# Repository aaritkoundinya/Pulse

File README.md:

# Pulse

Single-repo KiCad workspace for all Pulse board revisions.

## Repository Structure

- `boards/r2/` - imported from your existing `pulser2`
- `boards/r2.1/` - imported from your existing `pulser2.1`
- `templates/scratch-board/` - starter template for clean-slate revisions
- `tools/new_revision.sh` - helper script to create new revisions

Each board folder has its own KiCad-focused `.gitignore`.

## Create New Revisions

Build from an existing revision:

```bash
./tools/new_revision.sh r3 --from r2.1
```

Start from scratch:

```bash
./tools/new_revision.sh r3 --scratch
```

After creation, open KiCad and work in `boards/<revision>/`.

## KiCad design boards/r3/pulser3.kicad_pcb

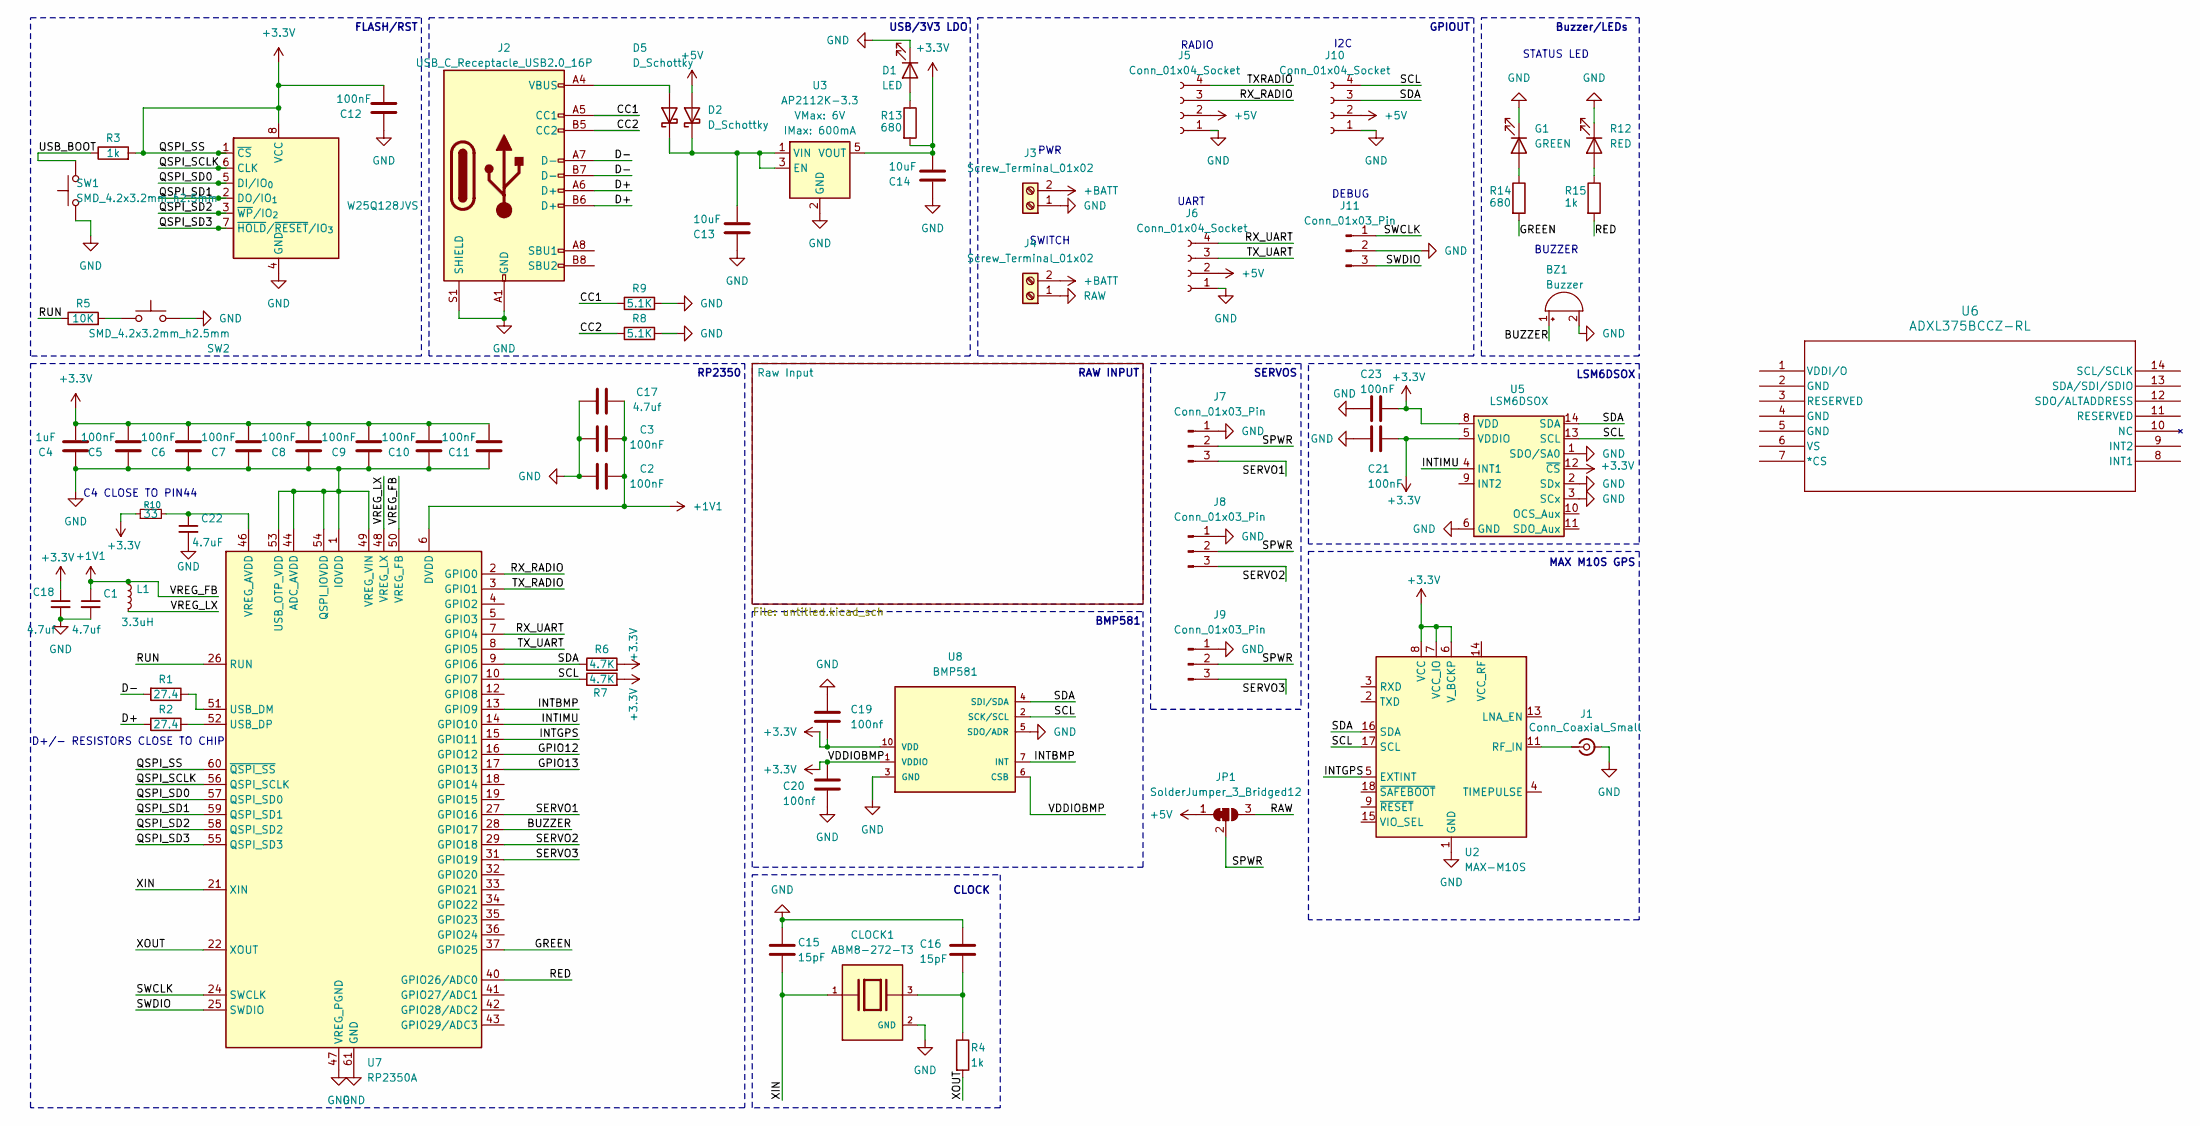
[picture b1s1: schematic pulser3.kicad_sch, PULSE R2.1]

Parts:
BZ1: Buzzer; Buzzer_CUI_CPT-9019S-SMT
C1, C17, C18: 4.7uf; C_0402_1005Metric
C2, C3, C5, C6, C7, C8, C9, C10, C11, C12, C21, C23: 100nF; C_0402_1005Metric
C4: 1uF; C_0402_1005Metric
C13, C14: 10uF; C_0805_2012Metric
C15, C16: 15pF; C_0402_1005Metric
C19, C20: 100nf; C_0402_1005Metric
C22: 4.7uF; C_0402_1005Metric
CLOCK1: ABM8-272-T3; XTAL_ABM8-272-T3; PARTREV 07-29-20
D1: LED; LED_0603_1608Metric
D2, D5: D_Schottky; D_SOD-323_HandSoldering
G1: GREEN; LED_0603_1608Metric
J1: Conn_Coaxial_Small; U.FL_Molex_MCRF_73412-0110_Vertical
J2: USB_C_Receptacle_USB2.0_16P; USB_C_Receptacle_JAE_DX07S016JA1R1500
J3, J4: Screw_Terminal_01x02; TerminalBlock_Phoenix_MPT-0,5-2-2.54_1x02_P2.54mm_Horizontal
J5, J6, J10: Conn_01x04_Socket; JST_SH_BM04B-SRSS-TB_1x04-1MP_P1.00mm_Vertical
J7, J8, J9, J11: Conn_01x03_Pin; JST_SH_BM03B-SRSS-TB_1x03-1MP_P1.00mm_Vertical
JP1: SolderJumper_3_Bridged12; SolderJumper-3_P1.3mm_Open_RoundedPad1.0x1.5mm
L1: 3.3uH; Untitled
R1, R2: 27.4; R_0402_1005Metric
R3, R4, R15: 1k; R_0402_1005Metric
R5: 10K; R_0402_1005Metric
R6, R7: 4.7K; R_0402_1005Metric
R8, R9: 5.1K; R_0402_1005Metric
R10: 33; R_0402_1005Metric
R12: RED; LED_0603_1608Metric
R13, R14: 680; R_0402_1005Metric
SW1, SW2: SMD_4.2x3.2mm_h2.5mm; Push_SMD_4.2x3.2mm
U1: W25Q128JVS; WSON-8-1EP_6x5mm_P1.27mm_EP3.4x4.3mm
U2: MAX-M10S; ublox_MAX
U3: AP2112K-3.3; SOT23-5
U5: LSM6DSOX; ST_LGA-14L_2.5x3.0mm_P0.5mm_4x3
U6: ADXL375BCCZ-RL
U7: RP2350A; QFN-60-1EP_7x7mm_P0.4mm_EP3.4x3.4mm
U8: BMP581

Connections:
+1V1: C1.1, C2.2, C3.2, C17.2, L1.1, U7.6 (DVDD), U7.23 (DVDD), U7.39 (DVDD), U7.50 (VREG_FB)
+3.3V: C4.1, C5.1, C6.1, C7.1, C8.1, C9.1, C10.1, C11.1, C12.1, C14.1, C18.1, C19.2, C20.1, C21.2, C23.2, R3.2, R6.2, R7.2, R10.1, R13.2, U1.1 (~CS), U1.8 (VCC), U2.6 (V_BCKP), U2.7 (VCC_IO), U2.8 (VCC), U3.5 (VOUT), U5.5 (VDDIO), U5.8 (VDD), U5.12 (~CS), U7.60 (~QSPI_SS), U8.1 (VDDIO), U8.6 (CSB), U8.10 (VDD)
+5V: D2.2 (A), J5.2, J6.2, J10.2, JP1.1 (A)
+BATT: J3.2, J4.2
/BUZZER: BZ1.1 (+), U7.28 (GPIO17)
/CC1: J2.A5 (CC1), R9.1
/CC2: J2.B5 (CC2), R8.1
/D+: J2.A6 (D+), J2.B6 (D+), R2.2
/D-: J2.A7 (D-), J2.B7 (D-), R1.2
/GPIO12: U7.16 (GPIO12)
/GPIO13: U7.17 (GPIO13)
/GREEN: R14.2, U7.37 (GPIO25)
/INTBMP: U7.13 (GPIO9), U8.7 (INT)
/INTGPS: U2.5 (EXTINT), U7.15 (GPIO11)
/INTIMU: U5.4 (INT1), U7.14 (GPIO10)
/QSPI_SCLK: U1.6 (CLK), U7.56 (QSPI_SCLK)
/QSPI_SD0: U1.5 (DI/IO_{0}), U7.57 (QSPI_SD0)
/QSPI_SD1: U1.2 (DO/IO_{1}), U7.59 (QSPI_SD1)
/QSPI_SD2: U1.3 (~WP/IO_{2}), U7.58 (QSPI_SD2)
/QSPI_SD3: U1.7 (~HOLD/~RESET/IO_{3}), U7.55 (QSPI_SD3)
/RED: R15.2, U7.40 (GPIO26/ADC0)
/RUN: R5.1, U7.26 (RUN)
/RX_RADIO: J5.3, U7.2 (GPIO0)
/RX_UART: J6.4, U7.7 (GPIO4)
/SCL: J10.4, R7.1, U2.17 (SCL), U5.13 (SCL), U7.10 (GPIO7), U8.2 (SCK/SCL)
/SDA: J10.3, R6.1, U2.16 (SDA), U5.14 (SDA), U7.9 (GPIO6), U8.4 (SDI/SDA)
/SERVO1: J7.3, U7.27 (GPIO16)
/SERVO2: J8.3, U7.29 (GPIO18)
/SERVO3: J9.3, U7.31 (GPIO19)
/SPWR: J7.2, J8.2, J9.2, JP1.2 (C)
/SWCLK: J11.1, U7.24 (SWCLK)
/SWDIO: J11.3, U7.25 (SWDIO)
/TXRADIO: J5.4
/TX_RADIO: U7.3 (GPIO1)
/TX_UART: J6.3, U7.8 (GPIO5)
/USB_BOOT: R3.1, SW1.2
/VREG_LX: L1.2, U7.48 (VREG_LX)
/XIN: C15.2, CLOCK1.1, U7.21 (XIN)
/XOUT: R4.2, U7.22 (XOUT)
GND: BZ1.2 (-), C1.2, C2.1, C3.1, C4.2, C5.2, C6.2, C7.2, C8.2, C9.2, C10.2, C11.2, C12.2, C13.2, C14.2, C15.1, C16.1, C17.1, C18.2, C19.1, C20.2, C21.1, C22.2, C23.1, CLOCK1.2 (GND), CLOCK1.4 (GND), D1.1 (K), G1.1 (K), J1.2 (Ext), J2.A1 (GND), J2.A12 (GND), J2.B1 (GND), J2.B12 (GND), J2.S1 (SHIELD), J3.1, J5.1, J6.1, J7.1, J8.1, J9.1, J10.1, J11.2, R8.2, R9.2, R12.1 (K), SW1.1, SW2.2, U1.4 (GND), U2.1 (GND), U2.10 (GND), U2.12 (GND), U3.2 (GND), U5.1 (SDO/SA0), U5.2 (SDx), U5.3 (SCx), U5.6 (GND), U5.7 (GND), U7.1 (IOVDD), U7.11 (IOVDD), U7.20 (IOVDD), U7.30 (IOVDD), U7.38 (IOVDD), U7.44 (ADC_AVDD), U7.45 (IOVDD), U7.47 (VREG_PGND), U7.49 (VREG_VIN), U7.53 (USB_OTP_VDD), U7.54 (QSPI_IOVDD), U7.61 (GND), U8.3 (GND), U8.5 (SDO/ADR), U8.8 (GND), U8.9 (GND)
unnamed: C16.2, CLOCK1.3, R4.1
unnamed: D1.2 (A), R13.1
unnamed: C13.1, D2.1 (K), D5.1 (K), U3.1 (VIN), U3.3 (EN)
unnamed: D5.2 (A), J2.A4 (VBUS), J2.A9 (VBUS), J2.B4 (VBUS), J2.B9 (VBUS)
unnamed: G1.2 (A), R14.1
unnamed: J1.1 (In), U2.11 (RF_IN)
unnamed: R5.2, SW2.1
unnamed: R12.2 (A), R15.1
unnamed: R1.1, U7.51 (USB_DM)
unnamed: R2.1, U7.52 (USB_DP)
unnamed: C22.1, R10.2, U7.46 (VREG_AVDD)
RAW: J4.1, JP1.3 (B)

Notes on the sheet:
MAX M10S GPS
PWR
FLASH/RST
RP2350
USB/3V3 LDO
RAW INPUT
D+/- RESISTORS CLOSE TO CHIP
RADIO
C4 CLOSE TO PIN44
BUZZER
SERVOS
I2C
STATUS LED
SWITCH
BMP581
DEBUG
CLOCK
UART
LSM6DSOX
Buzzer/LEDs
GPIOUT

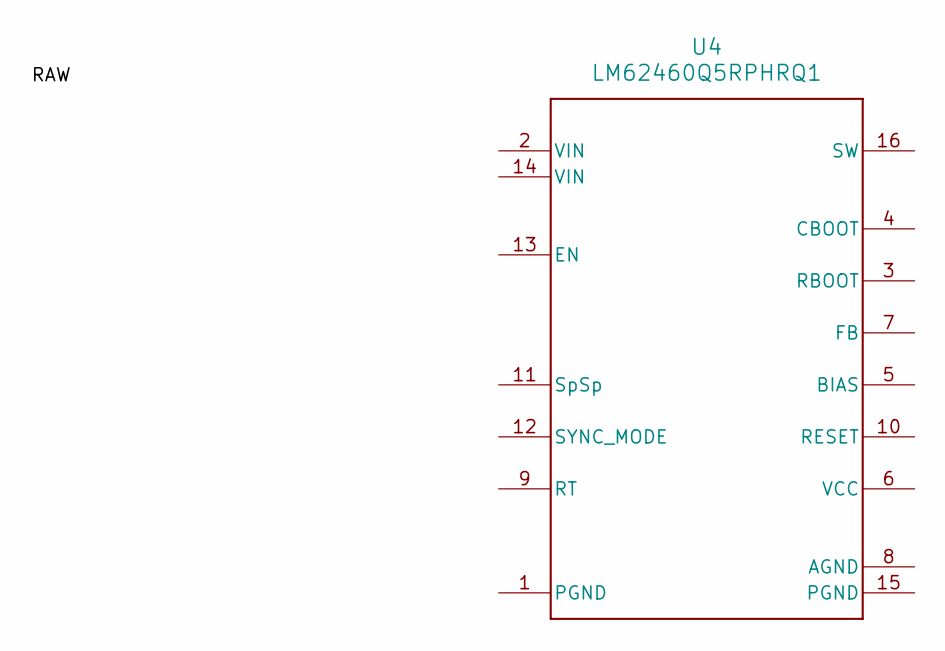
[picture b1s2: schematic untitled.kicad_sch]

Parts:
U4: LM62460Q5RPHRQ1

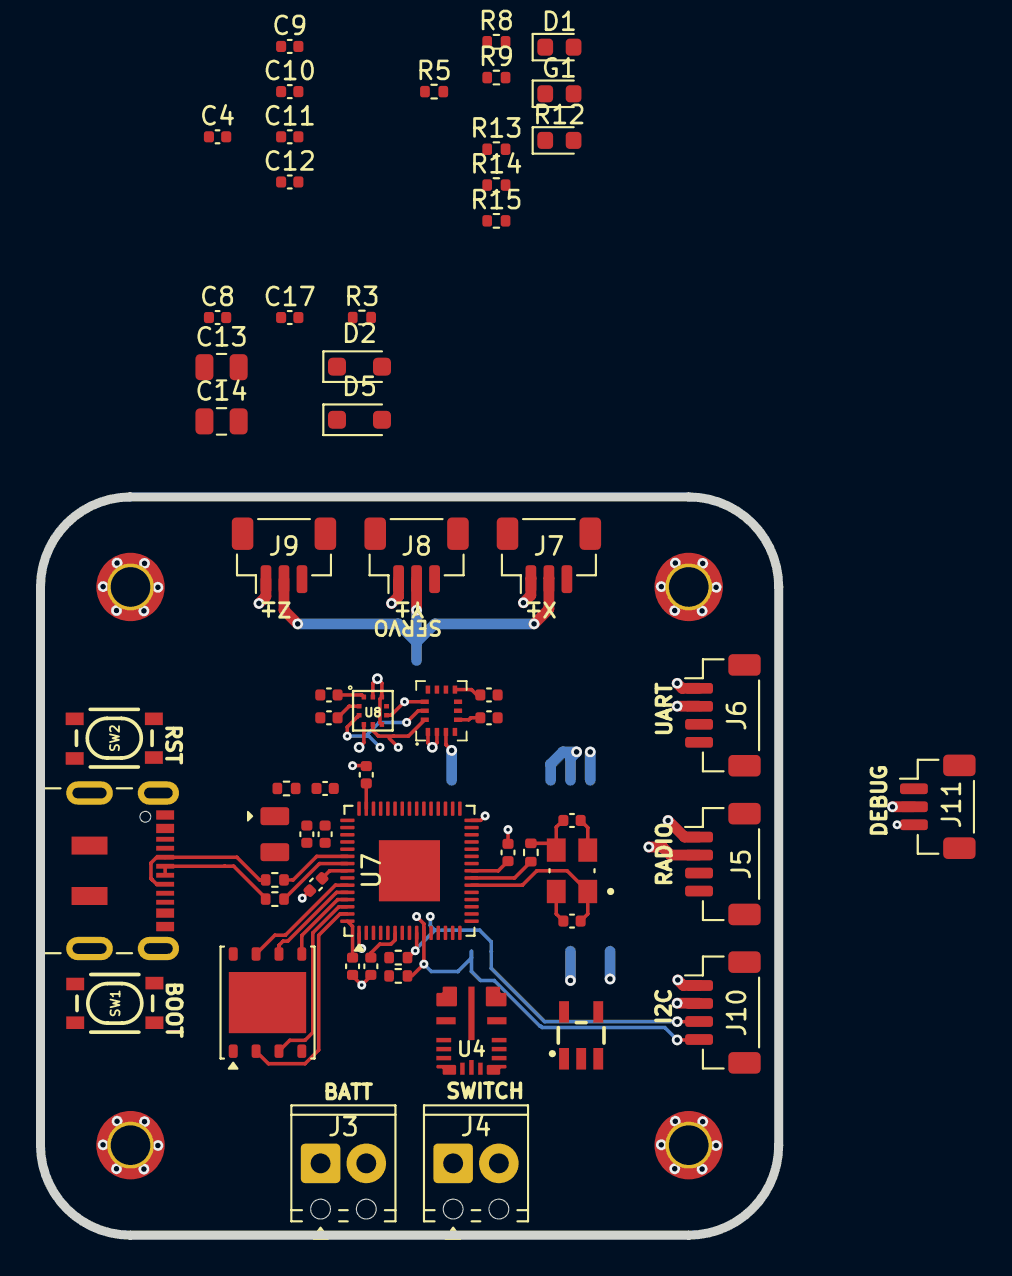
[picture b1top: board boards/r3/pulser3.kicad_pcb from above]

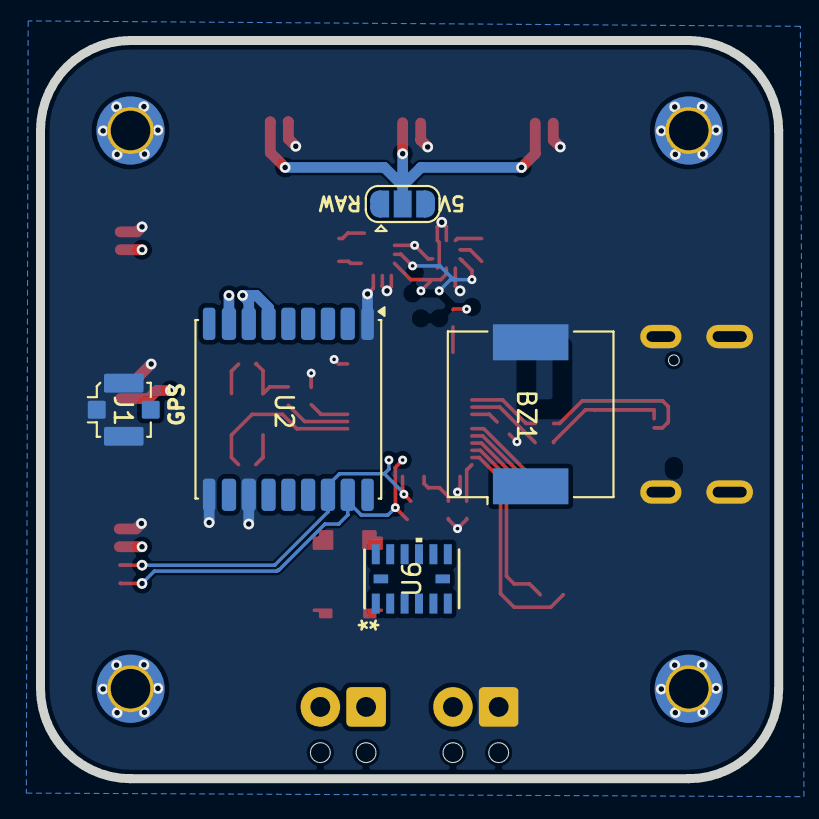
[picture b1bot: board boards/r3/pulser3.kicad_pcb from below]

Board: 4 copper layers, 41.0 x 41.0 mm, 66 parts (5 on the bottom side), 48 nets.

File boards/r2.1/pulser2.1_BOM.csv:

"Id";"Designator";"Footprint";"Quantity";"Designation";"Supplier and ref";
1;"U2";"SOT-23-5";1;"SPX3819M5-L-1-8";;;
2;"C28";"C_0603_1608Metric";1;"10nF";;;
3;"C25";"C_Elec_3x5.4";1;"2.2uF";;;
4;"R3,R4";"R_0603_1608Metric";2;"1k";;;
5;"C16,C15";"C_0603_1608Metric";2;"15pF";;;
6;"R6,R8,R9,R7";"R_0603_1608Metric";4;"4.7K";;;
7;"U1";"QFN-56-1EP_7x7mm_P0.4mm_EP3.2x3.2mm";1;"RP2040";;;
8;"C22,C21,C23";"C_0603_1608Metric";3;"0.1uF";;;
9;"PWR1,SW1";"PinHeader_1x02_P2.54mm_Vertical";2;"Conn_01x02_Pin";;;
10;"C20,C19";"C_0603_1608Metric";2;"100nf";;;
11;"C26,C27";"C_0603_1608Metric";2;"22uF";;;
12;"C17,C13,C14";"C_0603_1608Metric";3;"10uF";;;
13;"BZ1";"MagneticBuzzer_CUI_CMT-8504-100-SMT";1;"Buzzer";;;
14;"U3";"SOT23-5";1;"AP2112K-3.3";;;
15;"C24,C1,C4";"C_0603_1608Metric";3;"1uF";;;
16;"R5,R11";"R_0603_1608Metric";2;"10K";;;
17;"USB1";"USB_Micro-B_Wuerth_629105150521";1;"USB_B_Micro";;;
18;"IMU1";"InvenSense_QFN-24_3x3mm_P0.4mm";1;"ICM-20948";;;
19;"CLOCK1";"XTAL_ABM8-272-T3";1;"ABM8-272-T3";;;
20;"C18,C12,C9,C7,C10,C6,C8,C3,C11,C2,C5";"C_0603_1608Metric";11;"100nF";;;
21;"D2,D5";"D_0603_1608Metric";2;"D_Schottky";;;
22;"L1";"L_0603_1608Metric";1;"2.2uH";;;
23;"G1";"LED_0603_1608Metric";1;"GREEN";;;
24;"BMP1";"BMP581";1;"BMP581";;;
25;"R12";"LED_0603_1608Metric";1;"RED";;;
26;"SERVO1";"PinHeader_1x03_P2.54mm_Horizontal";1;"Conn_01x03_Pin";;;
27;"U6";"SOT-563";1;"AP62250Z6";;;
28;"BOOTSL1,RST1";"Push_SMD_4.2x3.2mm";2;"SMD_4.2x3.2mm_h2.5mm";;;
29;"R1,R2";"R_0603_1608Metric";2;"27.4";;;
30;"FLASH1";"SOIC-8_5.3x5.3mm_P1.27mm";1;"W25Q128JVS";;;
31;"RADIO1,GPIO1";"JST_PH_B4B-PH-K_1x04_P2.00mm_Vertical";2;"Conn_01x04_Socket";;;
32;"R10";"R_0603_1608Metric";1;"52.3K";;;
33;"D1";"LED_0603_1608Metric";1;"LED";;;

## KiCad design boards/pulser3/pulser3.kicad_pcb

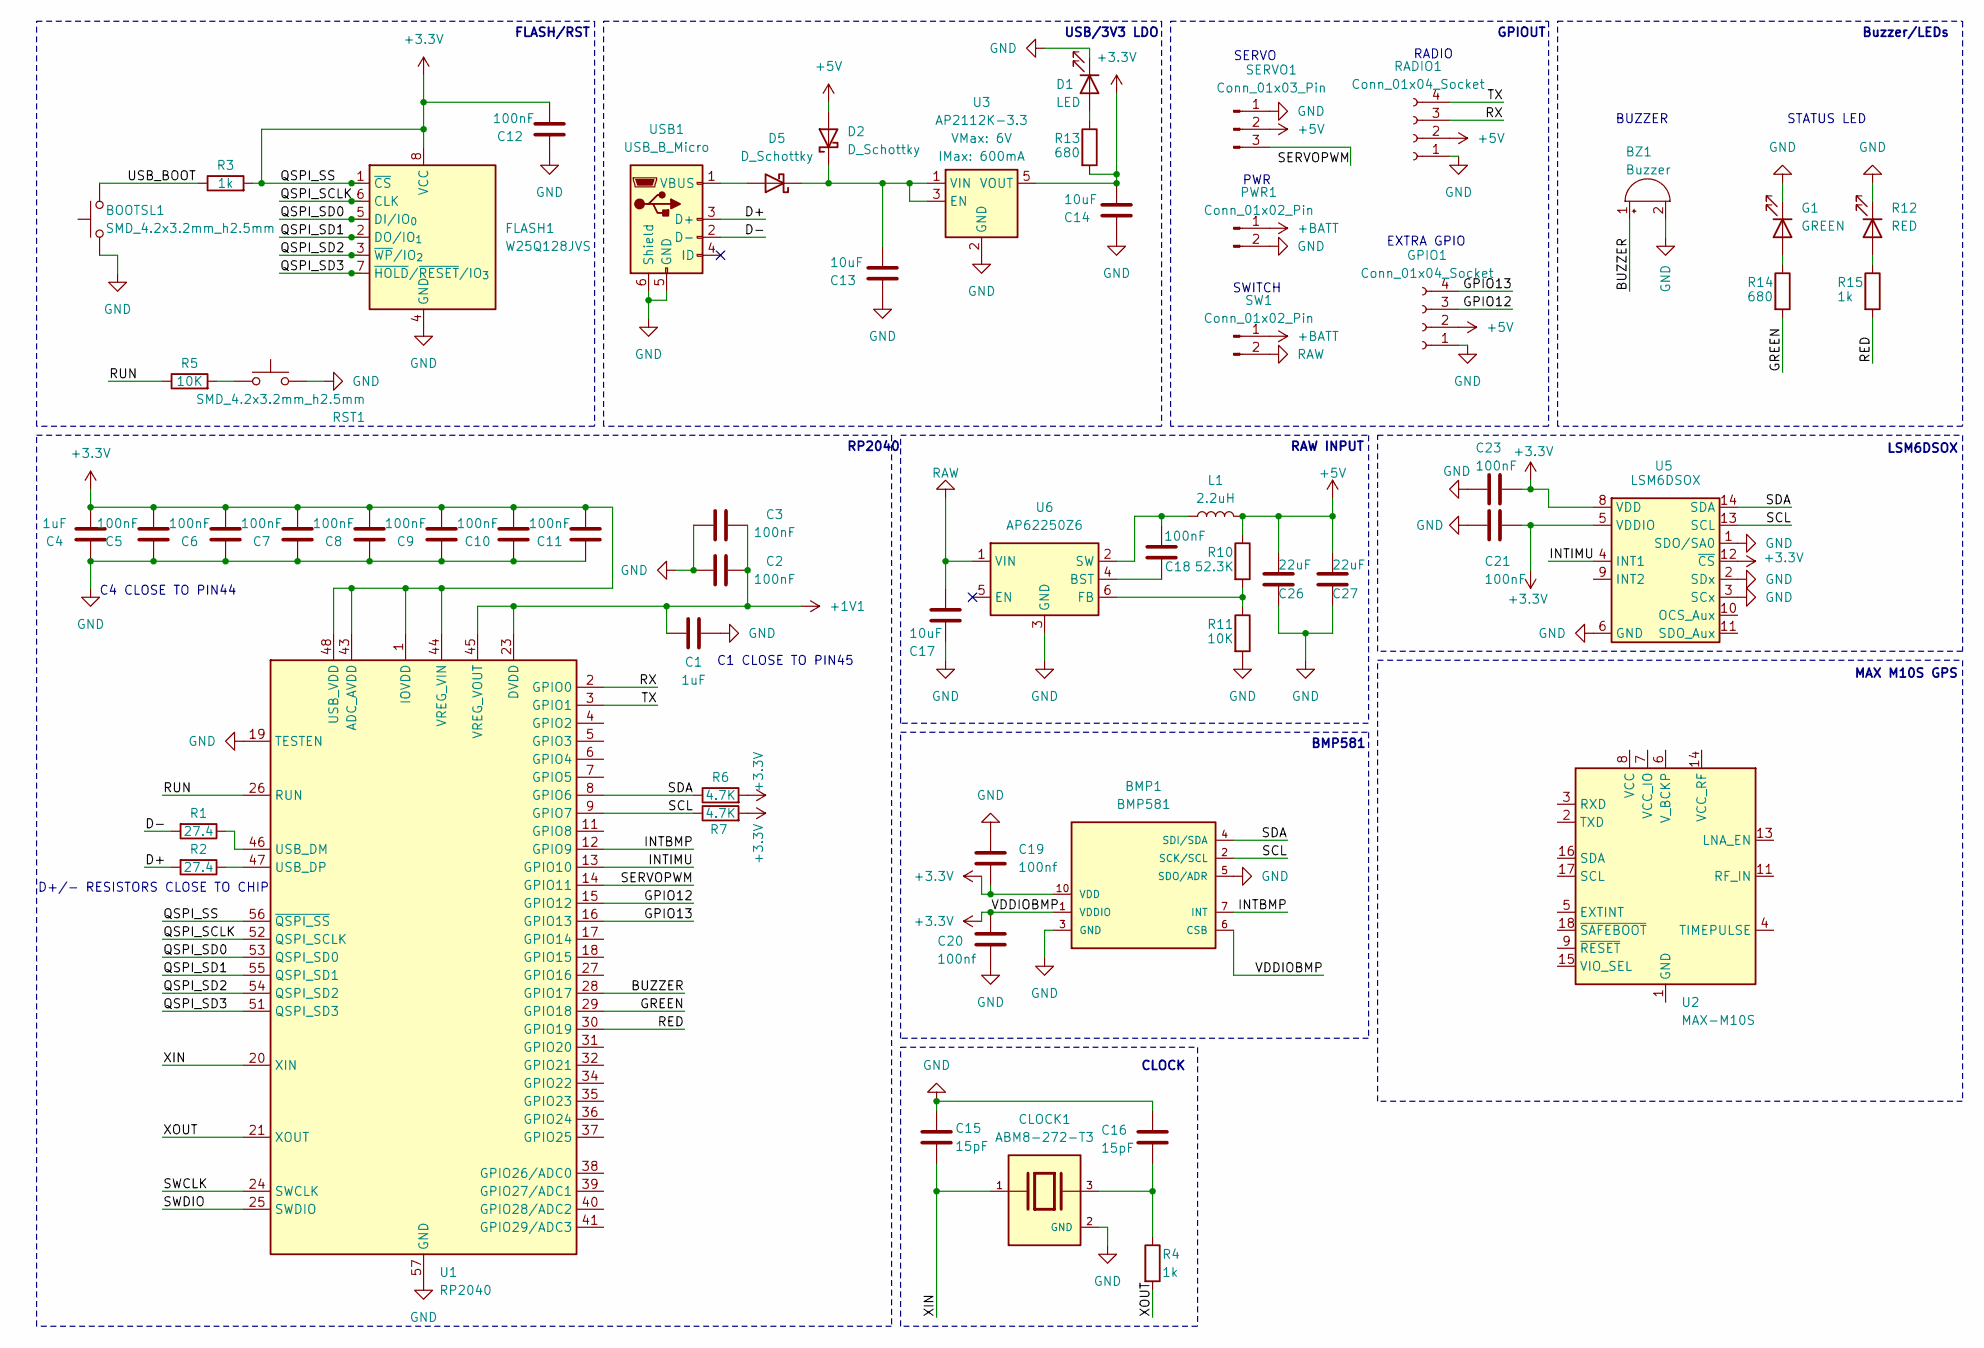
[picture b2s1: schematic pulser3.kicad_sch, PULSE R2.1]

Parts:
BMP1: BMP581
BOOTSL1: SMD_4.2x3.2mm_h2.5mm; Push_SMD_4.2x3.2mm
BZ1: Buzzer; Buzzer_CUI_CPT-9019S-SMT
C1, C4: 1uF; C_0603_1608Metric
C2, C3, C5, C6, C7, C8, C9, C10, C11, C12, C18, C21, C23: 100nF; C_0603_1608Metric
C13, C14, C17: 10uF; C_0805_2012Metric
C15, C16: 15pF; C_0603_1608Metric
C19, C20: 100nf; C_0603_1608Metric
C26, C27: 22uF; C_1206_3216Metric
CLOCK1: ABM8-272-T3; XTAL_ABM8-272-T3; PARTREV 07-29-20
D1: LED; LED_0603_1608Metric
D2, D5: D_Schottky; D_SOD-323_HandSoldering
FLASH1: W25Q128JVS; WSON-8-1EP_6x5mm_P1.27mm_EP3.4x4.3mm
G1: GREEN; LED_0603_1608Metric
GPIO1: Conn_01x04_Socket; JST_PH_B4B-PH-K_1x04_P2.00mm_Vertical
L1: 2.2uH; L_Vishay_IHLP-1616
PWR1: Conn_01x02_Pin; PinHeader_1x02_P2.54mm_Vertical
R1, R2: 27.4; R_0603_1608Metric
R3, R4: 1k; R_0603_1608Metric
R5, R11: 10K; R_0603_1608Metric
R6, R7: 4.7K; R_0603_1608Metric
R10: 52.3K; R_0603_1608Metric
R12: RED; LED_0603_1608Metric
R13, R14: 680; R_0402_1005Metric
R15: 1k; R_0402_1005Metric
RADIO1: Conn_01x04_Socket; JST_PH_B4B-PH-K_1x04_P2.00mm_Vertical
RST1: SMD_4.2x3.2mm_h2.5mm; Push_SMD_4.2x3.2mm
SERVO1: Conn_01x03_Pin; PinHeader_1x03_P2.54mm_Horizontal
SW1: Conn_01x02_Pin; PinHeader_1x02_P2.54mm_Vertical
U1: RP2040; QFN-56-1EP_7x7mm_P0.4mm_EP3.2x3.2mm
U2: MAX-M10S; ublox_MAX
U3: AP2112K-3.3; SOT23-5
U5: LSM6DSOX; ST_LGA-14L_2.5x3.0mm_P0.5mm_4x3
U6: AP62250Z6; SOT-563
USB1: USB_B_Micro; USB_Micro-B_Wuerth_629105150521

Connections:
+1V1: C1.1, C2.2, C3.2, U1.23 (DVDD), U1.45 (VREG_VOUT), U1.50 (DVDD)
+3.3V: BMP1.1 (VDDIO), BMP1.6 (CSB), BMP1.10 (VDD), C4.1, C5.1, C6.1, C7.1, C8.1, C9.1, C10.1, C11.1, C12.1, C14.1, C19.2, C20.1, C21.2, C23.2, FLASH1.1 (~CS), FLASH1.8 (VCC), R3.2, R6.2, R7.2, R13.2, U1.1 (IOVDD), U1.10 (IOVDD), U1.22 (IOVDD), U1.33 (IOVDD), U1.42 (IOVDD), U1.43 (ADC_AVDD), U1.44 (VREG_VIN), U1.48 (USB_VDD), U1.49 (IOVDD), U1.56 (~QSPI_SS), U3.5 (VOUT), U5.5 (VDDIO), U5.8 (VDD), U5.12 (~CS)
+5V: C26.1, C27.1, D2.2 (A), GPIO1.2, L1.2, R10.1, RADIO1.2, SERVO1.2
+BATT: PWR1.1, SW1.1
/BUZZER: BZ1.1 (+), U1.28 (GPIO17)
/D+: R2.2, USB1.3 (D+)
/D-: R1.2, USB1.2 (D-)
/GPIO12: GPIO1.3, U1.15 (GPIO12)
/GPIO13: GPIO1.4, U1.16 (GPIO13)
/GREEN: R14.2, U1.29 (GPIO18)
/INTBMP: BMP1.7 (INT), U1.12 (GPIO9)
/INTIMU: U1.13 (GPIO10), U5.4 (INT1)
/QSPI_SCLK: FLASH1.6 (CLK), U1.52 (QSPI_SCLK)
/QSPI_SD0: FLASH1.5 (DI/IO_{0}), U1.53 (QSPI_SD0)
/QSPI_SD1: FLASH1.2 (DO/IO_{1}), U1.55 (QSPI_SD1)
/QSPI_SD2: FLASH1.3 (~WP/IO_{2}), U1.54 (QSPI_SD2)
/QSPI_SD3: FLASH1.7 (~HOLD/~RESET/IO_{3}), U1.51 (QSPI_SD3)
/RED: R15.2, U1.30 (GPIO19)
/RUN: R5.1, U1.26 (RUN)
/RX: RADIO1.3, U1.2 (GPIO0)
/SCL: BMP1.2 (SCK/SCL), R7.1, U1.9 (GPIO7), U5.13 (SCL)
/SDA: BMP1.4 (SDI/SDA), R6.1, U1.8 (GPIO6), U5.14 (SDA)
/SERVOPWM: SERVO1.3, U1.14 (GPIO11)
/SWCLK: U1.24 (SWCLK)
/SWDIO: U1.25 (SWDIO)
/TX: RADIO1.4, U1.3 (GPIO1)
/USB_BOOT: BOOTSL1.2, R3.1
/XIN: C15.2, CLOCK1.1, U1.20 (XIN)
/XOUT: R4.2, U1.21 (XOUT)
GND: BMP1.3 (GND), BMP1.5 (SDO/ADR), BMP1.8 (GND), BMP1.9 (GND), BOOTSL1.1, BZ1.2 (-), C1.2, C2.1, C3.1, C4.2, C5.2, C6.2, C7.2, C8.2, C9.2, C10.2, C11.2, C12.2, C13.2, C14.2, C15.1, C16.1, C17.2, C19.1, C20.2, C21.1, C23.1, C26.2, C27.2, CLOCK1.2 (GND), CLOCK1.4 (GND), D1.1 (K), FLASH1.4 (GND), G1.1 (K), GPIO1.1, PWR1.2, R11.2, R12.1 (K), RADIO1.1, RST1.2, SERVO1.1, U1.19 (TESTEN), U1.57 (GND), U3.2 (GND), U5.1 (SDO/SA0), U5.2 (SDx), U5.3 (SCx), U5.6 (GND), U5.7 (GND), U6.3 (GND), USB1.5 (GND), USB1.6 (Shield)
unnamed: C16.2, CLOCK1.3, R4.1
unnamed: D1.2 (A), R13.1
unnamed: C13.1, D2.1 (K), D5.1 (K), U3.1 (VIN), U3.3 (EN)
unnamed: D5.2 (A), USB1.1 (VBUS)
unnamed: G1.2 (A), R14.1
unnamed: R5.2, RST1.1
unnamed: R12.2 (A), R15.1
unnamed: R1.1, U1.46 (USB_DM)
unnamed: R2.1, U1.47 (USB_DP)
unnamed: U2.1 (GND), U2.10 (GND), U2.12 (GND)
unnamed: C18.2, U6.4 (BST)
unnamed: R10.2, R11.1, U6.6 (FB)
unnamed: C18.1, L1.1, U6.2 (SW)
RAW: C17.1, SW1.2, U6.1 (VIN)

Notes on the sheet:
MAX M10S GPS
PWR
FLASH/RST
RP2040
USB/3V3 LDO
RAW INPUT
D+/- RESISTORS CLOSE TO CHIP
RADIO
SERVO
C4 CLOSE TO PIN44
BUZZER
C1 CLOSE TO PIN45
STATUS LED
SWITCH
BMP581
CLOCK
EXTRA GPIO
LSM6DSOX
Buzzer/LEDs
GPIOUT

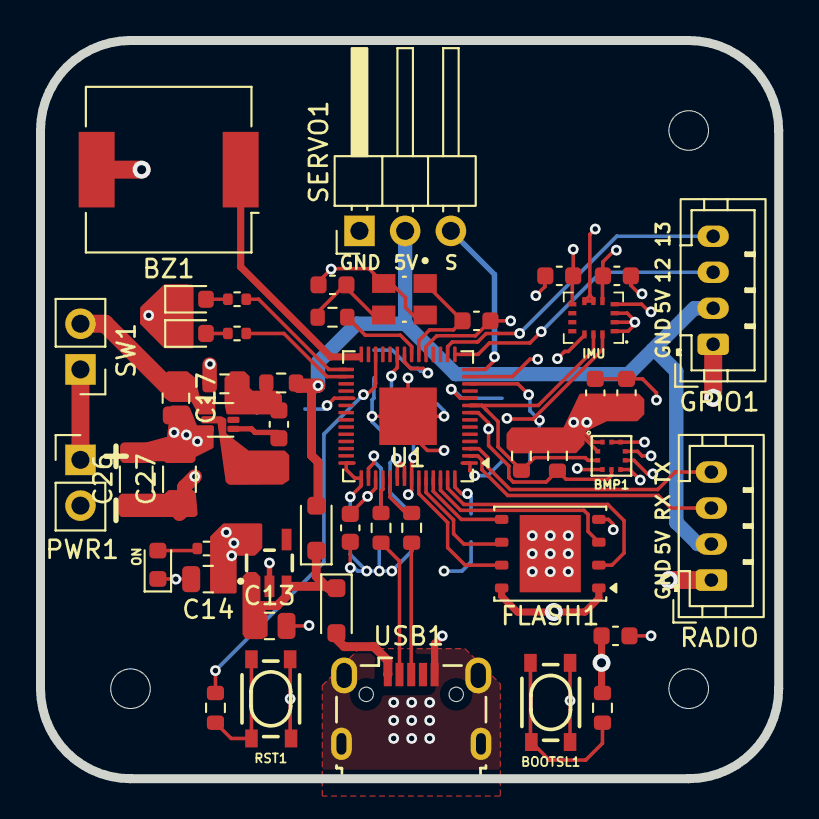
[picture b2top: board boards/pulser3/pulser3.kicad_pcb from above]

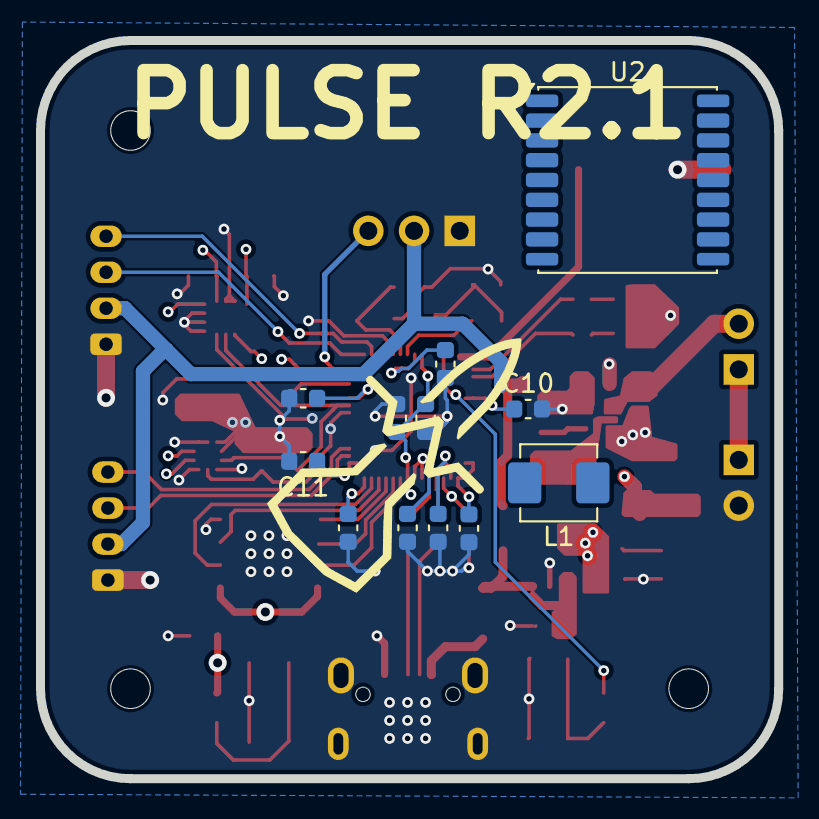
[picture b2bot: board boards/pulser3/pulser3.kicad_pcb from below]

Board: 4 copper layers, 41.0 x 41.0 mm, 59 parts (12 on the bottom side), 42 nets.

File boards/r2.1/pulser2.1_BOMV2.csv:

"Id";"Designator";"Footprint";"Quantity";"Designation";"Supplier and ref";
1;"R3,R4";"R_0603_1608Metric";2;"1k";;;
2;"C21,C18,C12,C23,C9,C7,C10,C6,C8,C3,C11,C2,C5";"C_0603_1608Metric";13;"100nF";;;
3;"C16,C15";"C_0603_1608Metric";2;"15pF";;;
4;"U1";"QFN-56-1EP_7x7mm_P0.4mm_EP3.2x3.2mm";1;"RP2040";;;
5;"PWR,SW1";"PinHeader_1x02_P2.54mm_Vertical";2;"Conn_01x02_Pin";;;
6;"C20,C19";"C_0603_1608Metric";2;"100nf";;;
7;"C26,C27";"C_0603_1608Metric";2;"22uF";;;
8;"C17,C13,C14";"C_0603_1608Metric";3;"10uF";;;
9;"BZ";"Buzzer_CUI_CPT-9019S-SMT";1;"Buzzer";;;
10;"U3";"SOT23-5";1;"AP2112K-3.3";;;
11;"U5";"ST_LGA-14L_2.5x3.0mm_P0.5mm_4x3";1;"LSM6DSOX";;;
12;"R5,R11";"R_0603_1608Metric";2;"10K";;;
13;"USB";"USB_Micro-B_Wuerth_629105150521";1;"USB_B_Micro";;;
14;"CLOCK1";"XTAL_ABM8-272-T3";1;"ABM8-272-T3";;;
15;"C1,C4";"C_0603_1608Metric";2;"1uF";;;
16;"D2,D5";"D_SOD-323_HandSoldering";2;"D_Schottky";;;
17;"L1";"L_0603_1608Metric";1;"2.2uH";;;
18;"G1";"LED_0603_1608Metric";1;"GREEN";;;
19;"BMP";"BMP581";1;"BMP581";;;
20;"R13,R14";"R_0402_1005Metric";2;"680";;;
21;"R12";"LED_0603_1608Metric";1;"RED";;;
22;"SERVO";"PinHeader_1x03_P2.54mm_Horizontal";1;"Conn_01x03_Pin";;;
23;"R6,R7";"R_0603_1608Metric";2;"4.7K";;;
24;"U6";"SOT-563";1;"AP62250Z6";;;
25;"BOOTSL,RST";"Push_SMD_4.2x3.2mm";2;"SMD_4.2x3.2mm_h2.5mm";;;
26;"R1,R2";"R_0603_1608Metric";2;"27.4";;;
27;"FLASH";"WSON-8-1EP_6x5mm_P1.27mm_EP3.4x4.3mm";1;"W25Q128JVS";;;
28;"RADIO1,GPIO";"JST_PH_B4B-PH-K_1x04_P2.00mm_Vertical";2;"Conn_01x04_Socket";;;
29;"R10";"R_0603_1608Metric";1;"52.3K";;;
30;"D1";"LED_0603_1608Metric";1;"LED";;;
31;"R15";"R_0402_1005Metric";1;"1k";;;

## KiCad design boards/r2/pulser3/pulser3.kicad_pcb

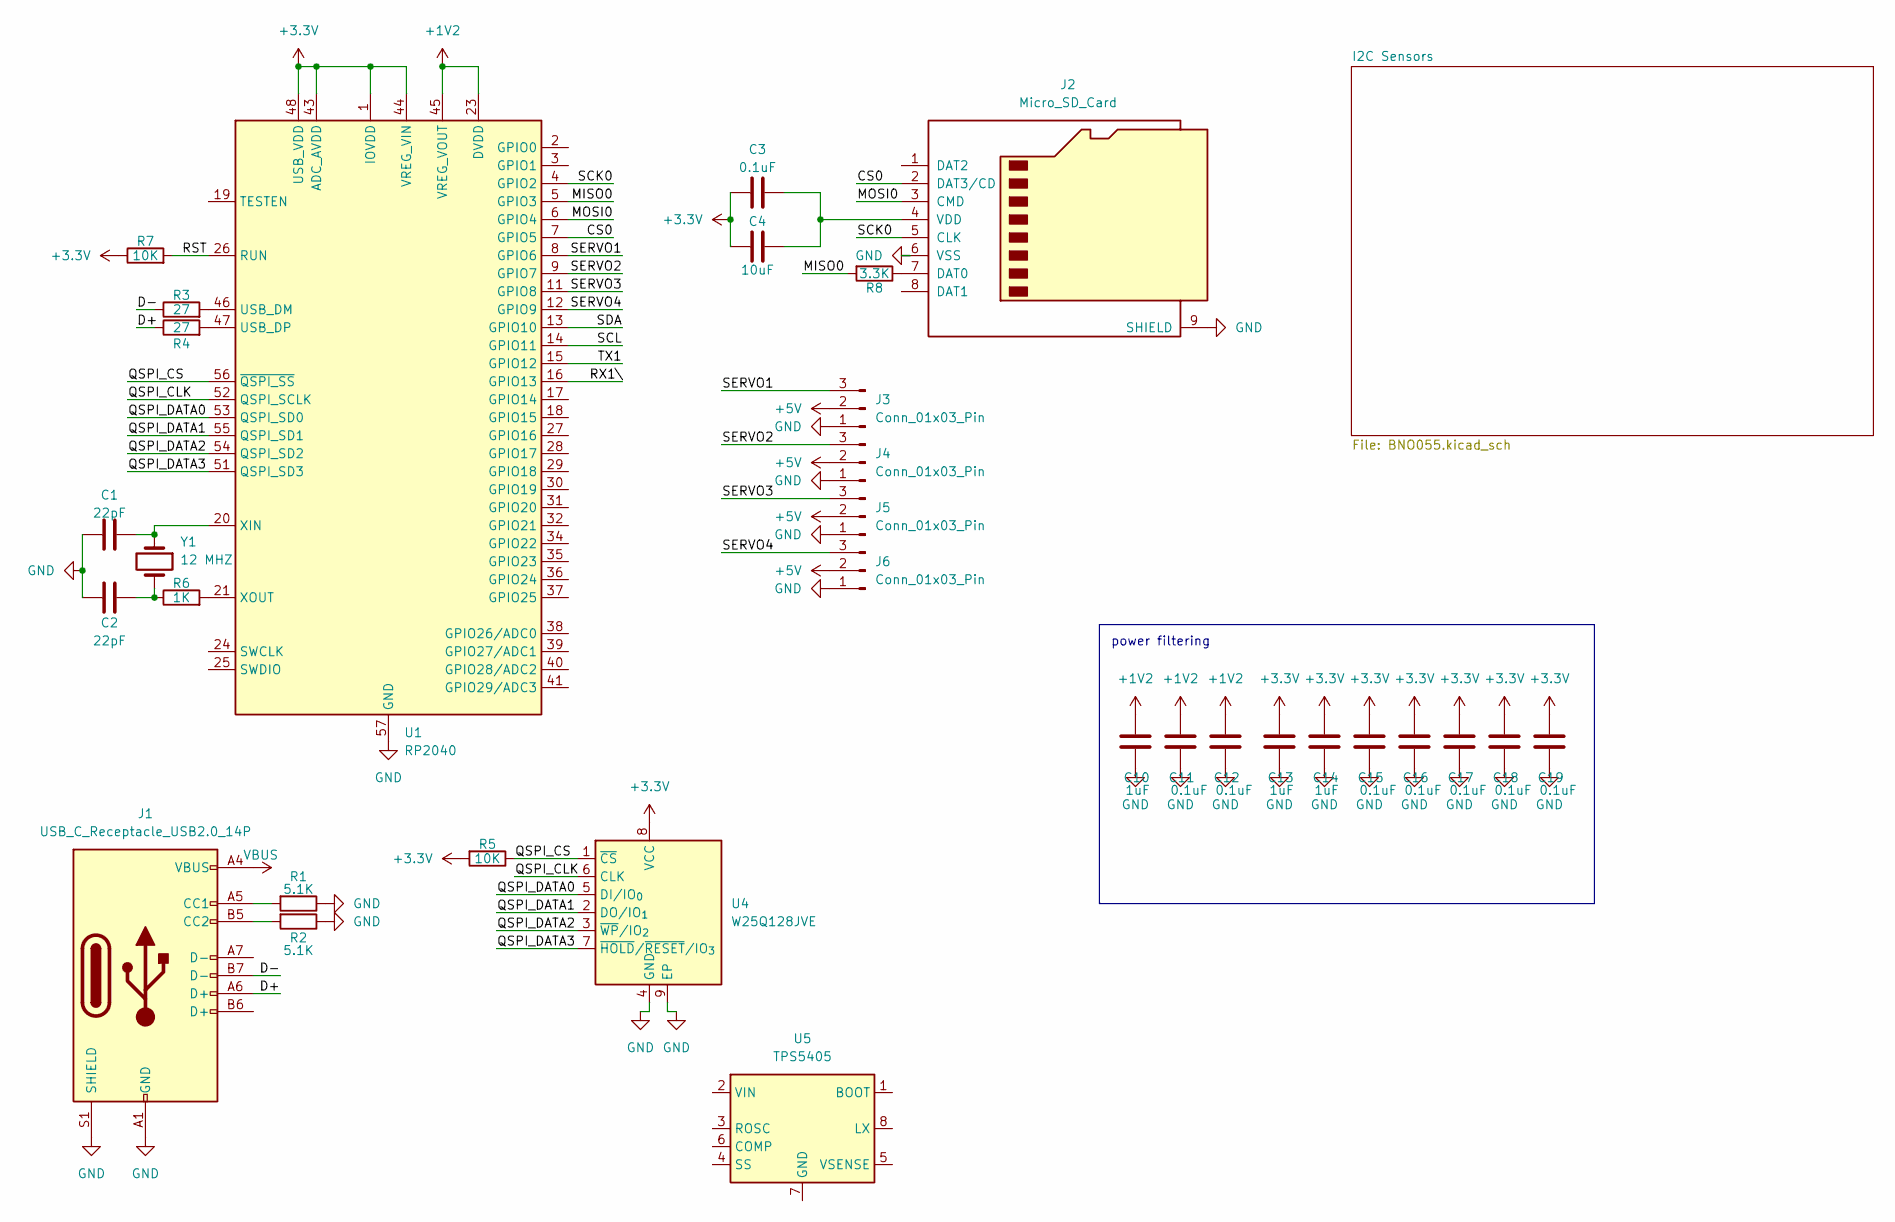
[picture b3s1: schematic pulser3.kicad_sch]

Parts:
C1, C2: 22pF; C_0805_2012Metric
C3, C11, C12, C15, C16, C17, C18, C19: 0.1uF; C_0805_2012Metric
C4: 10uF; C_0805_2012Metric
C10, C13, C14: 1uF; C_0805_2012Metric
J1: USB_C_Receptacle_USB2.0_14P; USB_C_Receptacle_GCT_USB4105-xx-A_16P_TopMnt_Horizontal
J2: Micro_SD_Card; microSD_HC_Hirose_DM3D-SF
J3, J4, J5, J6: Conn_01x03_Pin; PinHeader_1x03_P2.54mm_Vertical
R1, R2: 5.1K; R_0603_1608Metric
R3, R4: 27; R_0603_1608Metric
R5, R7: 10K; R_0603_1608Metric
R6: 1K; R_0603_1608Metric
R8: 3.3K; R_0603_1608Metric
U1: RP2040; QFN-56-1EP_7x7mm_P0.4mm_EP3.2x3.2mm
U4: W25Q128JVE; WSON-8-1EP_8x6mm_P1.27mm_EP3.4x4.3mm
U5: TPS5405; SOIC-8_3.9x4.9mm_P1.27mm
Y1: 12 MHZ; Crystal_SMD_3215-2Pin_3.2x1.5mm

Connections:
+1V2: C10.1, C11.1, C12.1, U1.23 (DVDD), U1.45 (VREG_VOUT), U1.50 (DVDD)
+5V: J3.2, J4.2, J5.2, J6.2
/CS0: J2.2 (DAT3/CD), U1.7 (GPIO5)
/D+: J1.A6 (D+), R4.1
/D-: J1.B7 (D-), R3.1
/MISO0: R8.2, U1.5 (GPIO3)
/MOSI0: J2.3 (CMD), U1.6 (GPIO4)
/QSPI_CLK: U1.52 (QSPI_SCLK), U4.6 (CLK)
/QSPI_CS: R5.1, U1.56 (~QSPI_SS), U4.1 (~CS)
/QSPI_DATA0: U1.53 (QSPI_SD0), U4.5 (DI/IO_{0})
/QSPI_DATA1: U1.55 (QSPI_SD1), U4.2 (DO/IO_{1})
/QSPI_DATA2: U1.54 (QSPI_SD2), U4.3 (~WP/IO_{2})
/QSPI_DATA3: U1.51 (QSPI_SD3), U4.7 (~HOLD/~RESET/IO_{3})
/RST: R7.2, U1.26 (RUN)
/RX1\: U1.16 (GPIO13)
/SCK0: J2.5 (CLK), U1.4 (GPIO2)
/SCL: U1.14 (GPIO11)
/SDA: U1.13 (GPIO10)
/SERVO1: J3.3, U1.8 (GPIO6)
/SERVO2: J4.3, U1.9 (GPIO7)
/SERVO3: J5.3, U1.11 (GPIO8)
/SERVO4: J6.3, U1.12 (GPIO9)
/TX1: U1.15 (GPIO12)
unnamed: C2.2, R6.1, Y1.2
unnamed: J1.A5 (CC1), R1.2
unnamed: J1.B5 (CC2), R2.2
unnamed: J2.7 (DAT0), R8.1
unnamed: C3.1, C4.1, J2.4 (VDD)
unnamed: R3.2, U1.46 (USB_DM)
unnamed: R4.2, U1.47 (USB_DP)
unnamed: C1.2, U1.20 (XIN), Y1.1
unnamed: R6.2, U1.21 (XOUT)
VBUS: J1.A4 (VBUS), J1.A9 (VBUS), J1.B4 (VBUS), J1.B9 (VBUS)

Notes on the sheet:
power filtering

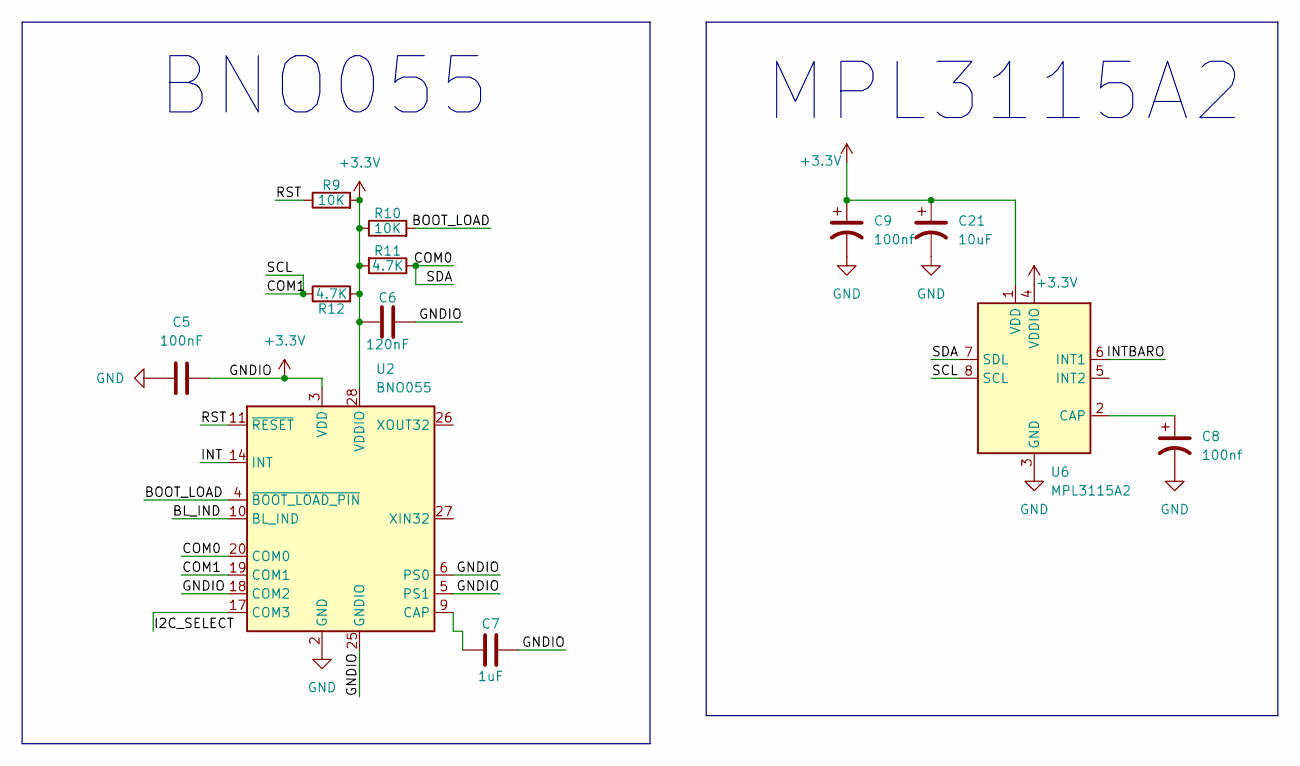
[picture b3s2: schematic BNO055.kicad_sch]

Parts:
C5: 100nF; C_0805_2012Metric
C6: 120nF; C_0805_2012Metric
C7: 1uF; C_0805_2012Metric
C8, C9: 100nf
C21: 10uF
R9, R10: 10K; R_0603_1608Metric
R11, R12: 4.7K; R_0603_1608Metric
U2: BNO055; LGA-28_5.2x3.8mm_P0.5mm
U6: MPL3115A2; NXP_LGA-8_3x5mm_P1.25mm_H1.1mm

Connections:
/I2C Sensors/BL_IND: U2.10 (BL_IND)
/I2C Sensors/BOOT_LOAD: R10.2, U2.4 (~BOOT_LOAD_PIN)
/I2C Sensors/COM0: R11.1, U2.20 (COM0), U6.7 (SDL); also elsewhere on the board
/I2C Sensors/COM1: R12.1, U2.19 (COM1), U6.8 (SCL); also elsewhere on the board
/I2C Sensors/I2C_SELECT: U2.17 (COM3)
/I2C Sensors/INT: U2.14 (INT)
/I2C Sensors/RST: R9.1, U2.11 (~RESET)
unnamed: C7.2, U2.9 (CAP)

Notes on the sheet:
BNO055
MPL3115A2

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
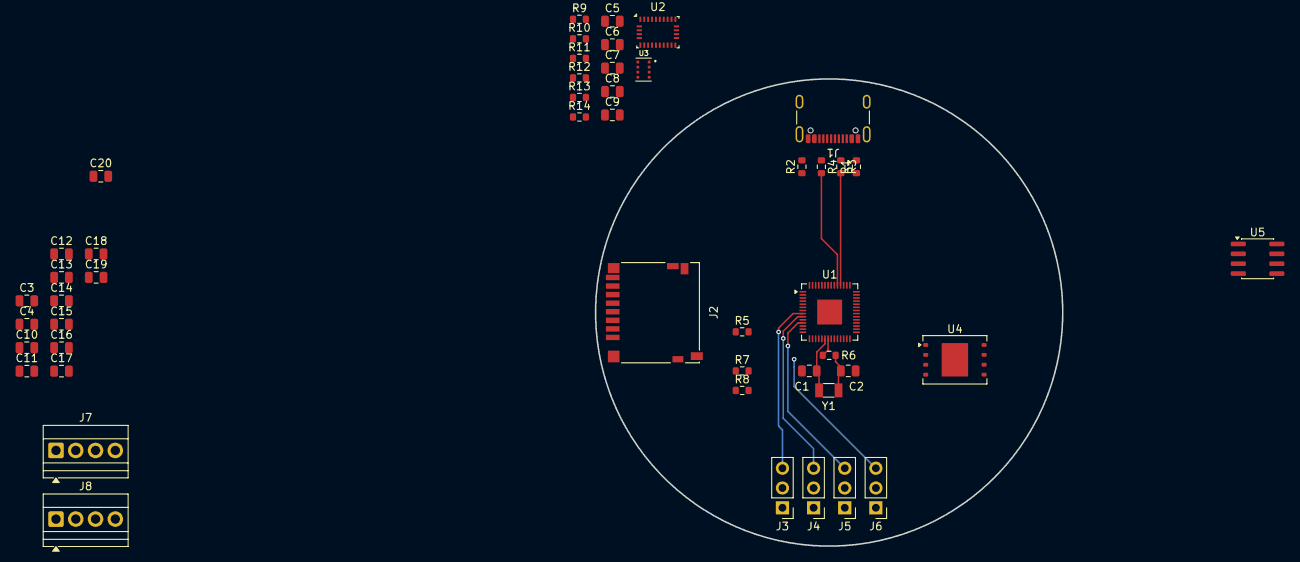
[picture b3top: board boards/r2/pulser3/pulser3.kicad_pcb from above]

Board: 4 copper layers, 60.0 x 60.0 mm, 48 parts (0 on the bottom side), 37 nets.

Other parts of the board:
C20: C; C_0805_2012Metric
J7, J8: Screw_Terminal_01x04; TerminalBlock_Xinya_XY308-2.54-4P_1x04_P2.54mm_Horizontal
R13, R14: 4.7K; R_0603_1608Metric
U3: DPS310XTSA1; XDCR_DPS310XTSA1

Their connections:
/I2C Sensors/COM0: R14.2, U3.3 (SDI); also elsewhere on the board
/I2C Sensors/COM1: R13.2, U3.4 (SCK); also elsewhere on the board
/I2C Sensors/VDDIO: R13.1, R14.1
